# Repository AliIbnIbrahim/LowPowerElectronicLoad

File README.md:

# LowPowerElectronicLoad
Low power High precision electronic load

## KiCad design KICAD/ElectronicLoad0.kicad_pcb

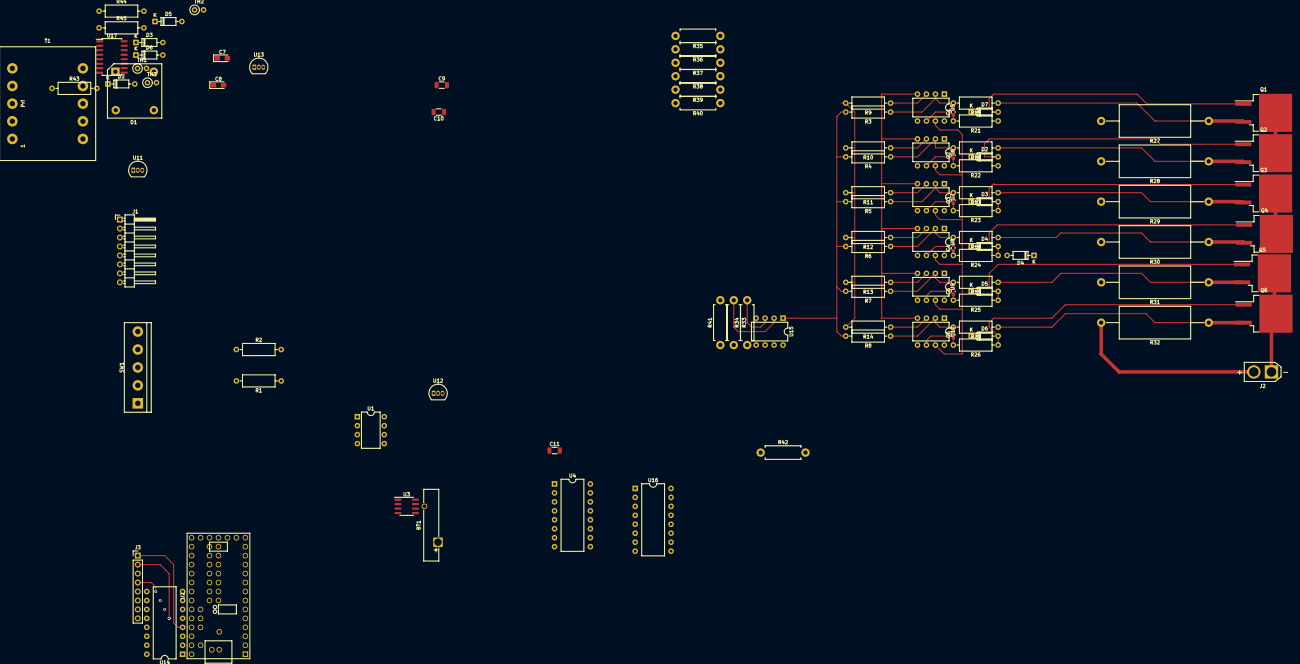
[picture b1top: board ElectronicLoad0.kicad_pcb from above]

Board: 2 copper layers, 100 parts (0 on the bottom side), 65 nets.

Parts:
BT1: Battery_Cell; Battery_Panasonic_CR2032-VS1N_Vertical_CircularHoles
C1, C2, C3, C4, C5, C6: 0.22n; C_0603_1608Metric_Pad1.08x0.95mm_HandSolder
C7, C8: 10µ; CP_EIA-3216-10_Kemet-I_Pad1.58x1.35mm_HandSolder
C9, C10, C11: 100n; C_1206_3216Metric
D1: D_Bridge_+-AA; Diode_Bridge_15.2x15.2x6.3mm_P10.9mm
D2, D2#2, D3, D3#2, D4, D4#2, D5, D5#2, D6, D6#2, D7: 1N4148; D_DO-35_SOD27_P7.62mm_Horizontal
J1: Conn_01x08; PinHeader_1x08_P2.54mm_Horizontal
J2: Conn_01x02_Female; AMASS_XT30U-M_1x02_P5.0mm_Vertical
J3: Conn_01x08_Male; PinHeader_1x08_P2.54mm_Vertical
Q1, Q2, Q3, Q4, Q5, Q6: STB15N80K5; TO-263-2
R1, R2: R_US; R_Axial_DIN0309_L9.0mm_D3.2mm_P12.70mm_Horizontal
R3, R4, R5, R6, R7, R8: 22k; R_Axial_DIN0309_L9.0mm_D3.2mm_P12.70mm_Horizontal
R9, R10, R11, R12, R13, R14, R15, R16, R17, R18, R19, R20, R43, R44, R45: 2k; R_Axial_DIN0309_L9.0mm_D3.2mm_P12.70mm_Horizontal
R21, R22, R23, R24, R25, R26: 100; R_Axial_DIN0309_L9.0mm_D3.2mm_P12.70mm_Horizontal
R27, R28, R29, R30, R31, R32: 0.1; R_Axial_DIN0922_L20.0mm_D9.0mm_P30.48mm_Horizontal
R33, R41: 100k; R_Axial_DIN0411_L9.9mm_D3.6mm_P12.70mm_Horizontal
R34: 15k; R_Axial_DIN0411_L9.9mm_D3.6mm_P12.70mm_Horizontal
R35, R36, R37, R38, R39, R40, R42: 10k; R_Axial_DIN0411_L9.9mm_D3.6mm_P12.70mm_Horizontal
SW1: Rotary_Encoder_Switch; TerminalBlock_bornier-5_P5.08mm
T1: Transformer_1P_2S; Transformer_CHK_EI30-2VA_2xSec
TH1, TH2, TH3: Thermistor; R_Axial_DIN0207_L6.3mm_D2.5mm_P2.54mm_Vertical
U1: DS1307+; DIP-8_W7.62mm
U2: Teensy3.2; Teensy30_31_32_All_Pins
U3: AT24CS32-SSHM; SOIC-8_3.9x4.9mm_P1.27mm
U4, U14, U16: PCF8574; DIP-16_W10.16mm
U5, U6, U7, U8, U9, U10: LF356; DIP-8_W7.62mm
U11: L78L12_TO92; TO-92_Inline
U12: L79L12_TO92; TO-92_Inline
U13: L78L05_TO92; TO-92_Inline
U15: LM358; DIP-8_W7.62mm
U17: PCF8591; SO-16_5.3x10.2mm_P1.27mm

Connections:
+5V: C11.1, R43.1, R44.1, R45.1, U1.8, U3.8, U4.16, U13.1, U14.1, U14.16, U16.2, U16.16, U17.16
+12V: C9.1, U5.7, U6.7, U7.7, U8.7, U9.7, U10.7, U11.1, U13.3
-12V: C10.2, U5.4, U6.4, U7.4, U8.4, U9.4, U10.4, U12.3
/keyb0: J3.1, U14.4
/keyb1: J3.2, U14.5
/keyb2: J3.3, U14.6
/keyb3: J3.4, U14.7
/keyb4: J3.5, U14.9
/keyb5: J3.6, U14.10
/keyb6: J3.7, U14.11
/keyb7: J3.8, U14.12
/onl1: D7.1, U16.4
/onl2: D2.1, U16.5
/onl3: D3.1, U16.6
/onl4: D4.1, U16.7
/onl5: D5.1, U16.9
/onl6: D6.1, U16.10
GND: BT1.2, C7.2, C8.2, C9.2, C10.1, C11.2, J2.2, R2.2, R9.2, R10.2, R11.2, R12.2, R13.2, R14.2, R27.2, R28.2, R29.2, R30.2, R31.2, R32.2, R34.1, T1.4, T1.5, TH1.2, TH2.2, TH3.2, U1.4, U2.1, U3.1, U3.2, U3.3, U3.4, U4.1, U4.2, U4.3, U4.8, U11.2, U12.1, U13.2, U14.2, U14.3, U14.8, U16.1, U16.3, U16.8, U17.5, U17.6, U17.7, U17.8
unnamed: BT1.1, U1.3
unnamed: C1.1, R21.2, U5.6
unnamed: C1.2, R3.1, R15.2, U5.2
unnamed: C2.1, R22.2, U6.6
unnamed: C2.2, R4.1, R16.2, U6.2
unnamed: C3.1, R23.2, U7.6
unnamed: C3.2, R5.1, R17.2, U7.2
unnamed: C4.1, R24.2, U8.6
unnamed: C4.2, R6.1, R18.2, U8.2
unnamed: C5.1, R25.2, U9.6
unnamed: C5.2, R7.1, R19.2, U9.2
unnamed: C6.1, R26.2, U10.6
unnamed: C6.2, R8.1, R20.2, U10.2
unnamed: C7.1, D1.3, T1.3, U11.3
unnamed: C8.1, D1.4, T1.6, U12.2
unnamed: D2.2, D2#2.2, Q2.1, R22.1
unnamed: D3.2, D3#2.2, Q3.1, R23.1
unnamed: D4.2, D4#2.2, Q4.1, R24.1
unnamed: D5.2, D5#2.2, Q5.1, R25.1
unnamed: D6.2, D6#2.2, Q6.1, R26.1
unnamed: D7.2, Q1.1, R21.1
unnamed: J2.1, Q1.2, Q2.2, Q3.2, Q4.2, Q5.2, Q6.2
unnamed: Q1.3, R15.1, R27.1, R35.1, U2.37
unnamed: Q2.3, R16.1, R28.1, R36.1, U2.54
unnamed: Q3.3, R17.1, R29.1, R37.1, U2.41
unnamed: Q4.3, R18.1, R30.1, R38.1, U2.50
unnamed: Q5.3, R19.1, R31.1, R39.1, U2.49
unnamed: Q6.3, R20.1, R32.1, R40.1, U2.48
unnamed: R1.1, U2.19
unnamed: R1.2, R2.1, R33.2
unnamed: R3.2, R4.2, R5.2, R6.2, R7.2, R8.2, R41.1, U15.1
unnamed: R9.1, U5.3
unnamed: R10.1, U6.3
unnamed: R11.1, U7.3
unnamed: R12.1, U8.3
unnamed: R13.1, U9.3
unnamed: R14.1, U10.3
unnamed: R33.1, R41.2, U15.2
unnamed: R34.2, U15.3
unnamed: R35.2, R36.2, R37.2, R38.2, R39.2, R40.2, U15.5
unnamed: R42.2, U15.6
unnamed: R43.2, TH1.1, U17.3
unnamed: R44.2, TH2.1, U17.2
unnamed: R45.2, TH3.1, U17.1
unnamed: U1.5, U2.25, U3.5, U4.15, U14.15, U16.15, U17.9
unnamed: U1.6, U2.26, U3.6, U4.14, U14.14, U16.14, U17.10
unnamed: U2.45, U15.7

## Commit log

2023-01-29 Copy files from disk
    Copy files from disk
